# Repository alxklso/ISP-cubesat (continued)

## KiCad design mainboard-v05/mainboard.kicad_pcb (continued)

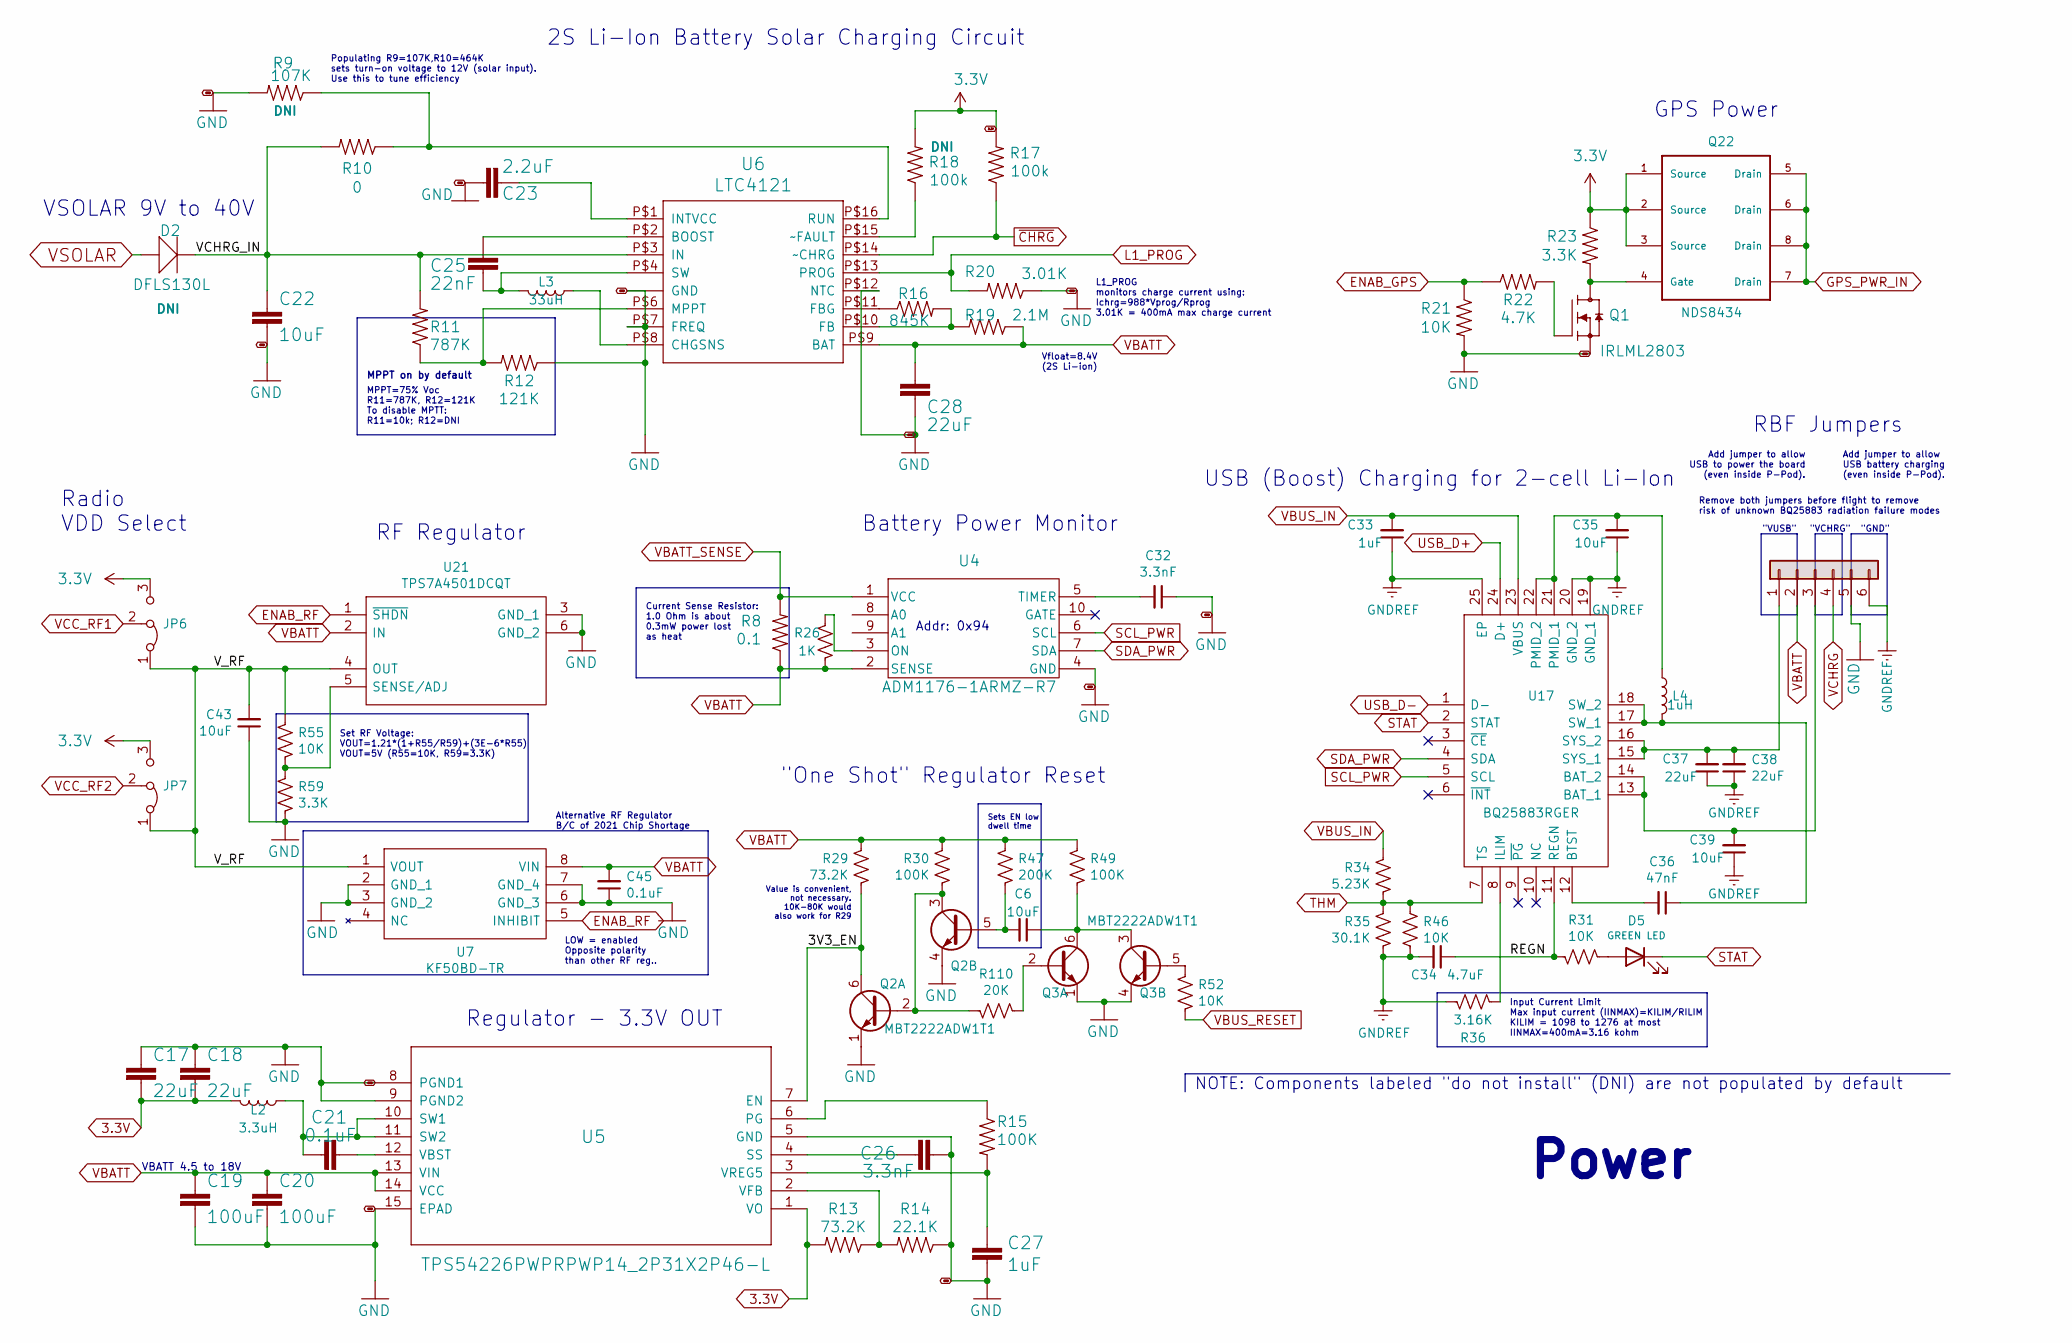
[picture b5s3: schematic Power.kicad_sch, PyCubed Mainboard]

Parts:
C6, C22, C35, C39, C43: 10uF; C_0603_1608Metric
C17, C18, C28, C37, C38: 22uF; C_0603_1608Metric
C19, C20: 100uF; C_1210_3225Metric
C21, C45: 0.1uF; C_0603_1608Metric
C23: 2.2uF; C_0603_1608Metric
C25: 22nF; C_0603_1608Metric
C26, C32: 3.3nF; C_0603_1608Metric
C27, C33: 1uF; C_0603_1608Metric
C34: 4.7uF; C_0603_1608Metric
C36: 47nF; C_0603_1608Metric
D2: DFLS130L; PWRDI-123; Manufacturer_Part_Number DFLS130L-7
D5: GREEN LED; LED_0603_1608Metric; Manufacturer_Part_Number LTST-C190KGKT
J14: Conn_01x06; PinHeader_1x06_P2.54mm_Vertical
JP6, JP7: Jumper_3_Bridged12; SolderJumper-3_P1.3mm_Bridged12_RoundedPad1.0x1.5mm
L2: 3.3uH; L_2141; Manufacturer_Part_Number HPC5040NF-3R3MTH
L3: 33uH; L_1812_4532Metric; Manufacturer_Part_Number SNR5040K-330M
L4: 1uH; L_2510; Manufacturer_Part_Number MCS25GD-1R0MMP
Q1: IRLML2803; SOT-23; Manufacturer_Part_Number IRLML2803TRPbF
Q2, Q3: MBT2222ADW1T1; SOT-363_SC-70-6; Manufacturer_Part_Number MBT2222ADW1T1G
Q22: NDS8434; Manufacturer_Part_Number NDS8434
R8: 0.1; R_2512_6332Metric
R9: 107K; R_0603_1608Metric
R10: 0; R_0603_1608Metric
R11: 787K; R_0603_1608Metric
R12: 121K; R_0603_1608Metric
R13, R29: 73.2K; R_0603_1608Metric
R14: 22.1K; R_0603_1608Metric
R15, R30, R49: 100K; R_0603_1608Metric
R16: 845K; R_0603_1608Metric
R17, R18: 100k; R_0603_1608Metric
R19: 2.1M; R_0603_1608Metric
R20: 3.01K; R_0603_1608Metric
R21, R31, R46, R52, R55: 10K; R_0603_1608Metric
R22: 4.7K; R_0603_1608Metric
R23, R59: 3.3K; R_0603_1608Metric
R26: 1K; R_0603_1608Metric
R34: 5.23K; R_0603_1608Metric
R35: 30.1K; R_0603_1608Metric
R36: 3.16K; R_0603_1608Metric
R47: 200K; R_0603_1608Metric
R110: 20K; R_0603_1608Metric
U4: ADM1176-1ARMZ-R7; Manufacturer_Part_Number ADM1176-1ARMZ-R7
U5: TPS54226PWPRPWP14_2P31X2P46-L; PWP14_2P31X2P46-L; Manufacturer_Part_Number TPS54226PWPR
U6: LTC4121; QFN-16-PAD; Manufacturer_Part_Number LTC4121EUD
U7: KF50BD-TR; SOIC127P600X175-8N; Manufacturer_Part_Number KF50BD-TR
U17: BQ25883RGER; QFN50P400X400X100-25N-D; Manufacturer_Part_Number BQ25883RGER
U21: TPS7A4501DCQT; Manufacturer_Part_Number TPS7A4501DCQT

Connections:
3.3V: C17.2, C18.2, JP6.3 (B), JP7.3 (B), L2.2, Q22.1 (Source), Q22.2 (Source), Q22.3 (Source), R13.2, R17.2, R18.2, R23.1, U5.1 (VO); also elsewhere on the board
/Power/3V3_EN: Q2.6 (C1), R29.2, U5.7 (EN)
/Power/REGN: C34.1, R31.2, U17.11 (REGN)
/Power/VCHRG_IN: C22.1, D2.C, R10.2, R11.2, U6.P$3 (IN)
/Power/V_RF: C43.2, JP6.1 (A), JP7.1 (A), R55.1, U7.1 (VOUT), U21.4 (OUT)
ENAB_GPS: R21.1, R22.1; also elsewhere on the board
ENAB_RF: U7.5 (INHIBIT), U21.1 (~SHDN); also elsewhere on the board
GND: C17.1, C18.1, C19.2, C20.2, C22.2, C23.2, C26.2, C27.2, C28.2, C32.1, C43.1, C45.1, J14.5, Q1.2 (S), Q2.1 (E1), Q2.4 (E2), Q3.1 (E1), Q3.4 (E2), R9.2, R12.1, R14.1, R20.1, R21.2, R59.2, U4.4 (GND), U5.5 (GND), U5.8 (PGND1), U5.9 (PGND2), U5.15 (EPAD), U6.P$5 (GND), U6.P$7 (FREQ), U6.P$12 (NTC), U6.P$17 (GND), U7.2 (GND_1), U7.3 (GND_2), U7.6 (GND_3), U7.7 (GND_4), U21.3 (GND_1), U21.6 (GND_2); also elsewhere on the board
GNDREF: C33.1, C34.2, C35.1, C37.1, C38.1, C39.1, J14.6, R35.1, R36.1, R46.1, U17.19 (GND_1), U17.20 (GND_2), U17.25 (EP); also elsewhere on the board
GPS_PWR_IN: Q22.5 (Drain), Q22.6 (Drain), Q22.7 (Drain), Q22.8 (Drain); also elsewhere on the board
L1_PROG: R20.2, U6.P$13 (PROG); also elsewhere on the board
unnamed: C6.1, Q3.3 (C2), Q3.6 (C1), R49.2
unnamed: C6.2, Q2.5 (B2), R47.2
unnamed: C21.1, L2.1, U5.10 (SW1), U5.11 (SW2)
unnamed: C21.2, U5.12 (VBST)
unnamed: C23.1, U6.P$1 (INTVCC)
unnamed: C25.1, U6.P$2 (BOOST)
unnamed: C25.2, L3.2, U6.P$4 (SW)
unnamed: C26.1, U5.4 (SS)
unnamed: C27.1, R15.2, U5.3 (VREG5)
unnamed: C32.2, U4.5 (TIMER)
unnamed: C35.2, L4.1, U17.21 (PMID_1), U17.22 (PMID_2)
unnamed: C36.1, L4.2, U17.17 (SW_1), U17.18 (SW_2)
unnamed: C36.2, U17.12 (BTST)
unnamed: C37.2, C38.2, J14.1, U17.15 (SYS_1), U17.16 (SYS_2)
unnamed: C39.2, J14.3, U17.13 (BAT_1), U17.14 (BAT_2)
unnamed: D5.2 (A), R31.1
unnamed: L3.1, U6.P$8 (CHGSNS)
unnamed: Q1.1 (G), R22.2
unnamed: Q1.3 (D), Q22.4 (Gate), R23.2
unnamed: Q2.2 (B1), Q2.3 (C2), R30.2, R110.2
unnamed: Q3.2 (B1), R110.1
unnamed: Q3.5 (B2), R52.1
unnamed: R9.1, R10.1, U6.P$16 (RUN)
unnamed: R11.1, R12.2, U6.P$6 (MPPT)
unnamed: R13.1, R14.2, U5.2 (VFB)
unnamed: R15.1, U5.6 (PG)
unnamed: R16.1, U6.P$11 (FBG)
unnamed: R16.2, R19.2, U6.P$10 (FB)
unnamed: R18.1, U6.P$15 (~FAULT)
unnamed: R26.2, U4.3 (ON)
unnamed: R36.2, U17.8 (ILIM)
unnamed: R55.2, R59.1, U21.5 (SENSE/ADJ)
SCL_PWR: U4.6 (SCL), U17.5 (SCL); also elsewhere on the board
SDA_PWR: U4.7 (SDA), U17.4 (SDA); also elsewhere on the board
STAT: D5.1 (K), U17.2 (STAT)
THM: R34.2, R35.2, R46.2, U17.7 (TS)
USB_D+: U17.24 (D+); also elsewhere on the board
USB_D-: U17.1 (D-); also elsewhere on the board
VBATT: C19.1, C20.1, C28.1, C45.2, J14.2, R8.1, R19.1, R26.1, R29.1, R30.1, R47.1, R49.1, U4.2 (SENSE), U5.13 (VIN), U5.14 (VCC), U6.P$9 (BAT), U7.8 (VIN), U21.2 (IN); also elsewhere on the board
VBATT_SENSE: R8.2, U4.1 (VCC); also elsewhere on the board
VBUS_IN: C33.2, R34.1, U17.23 (VBUS); also elsewhere on the board
VBUS_RESET: R52.2; also elsewhere on the board
VCC_RF1: JP6.2 (C); also elsewhere on the board
VCC_RF2: JP7.2 (C); also elsewhere on the board
VCHRG: J14.4; also elsewhere on the board
VSOLAR: D2.A; also elsewhere on the board
~CHRG: R17.1, U6.P$14 (~CHRG); also elsewhere on the board

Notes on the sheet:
Populating R9=107K,R10=464K sets turn-on voltage to 12V (solar input). Use this to tune efficiency
Set RF Voltage: VOUT=1.21*(1+R55/R59)+(3E-6*R55) VOUT=5V (R55=10K, R59=3.3K)
Vfloat=8.4V (2S Li-ion)
"One Shot" Regulator Reset
Battery Power Monitor
Value is convenient, not necessary. 10K-80K would also work for R29
MPPT=75% Voc R11=787K, R12=121K To disable MPTT: R11=10k; R12=DNI
"GND"
"VUSB"
L1_PROG monitors charge current using: Ichrg=988*Vprog/Rprog 3.01K = 400mA max charge current
Regulator - 3.3V OUT
Alternative RF Regulator B/C of 2021 Chip Shortage
Remove both jumpers before flight to remove risk of unknown BQ25883 radiation failure modes
NOTE: Components labeled "do not install" (DNI) are not populated by default
Input Current Limit Max input current (IINMAX)=KILIM/RILIM KILIM = 1098 to 1276 at most IINMAX=400mA=3.16 kohm
Power
RBF Jumpers
Addr: 0x94
VSOLAR 9V to 40V
GPS Power
LOW = enabled Opposite polarity than other RF reg..
2S Li-Ion Battery Solar Charging Circuit
Add jumper to allow USB to power the board (even inside P-Pod).
USB (Boost) Charging for 2-cell Li-Ion
RF Regulator
Radio VDD Select
"VCHRG"
Sets EN low dwell time
Add jumper to allow USB battery charging (even inside P-Pod).
MPPT on by default
VBATT 4.5 to 18V
Current Sense Resistor: 1.0 Ohm is about 0.3mW power lost as heat

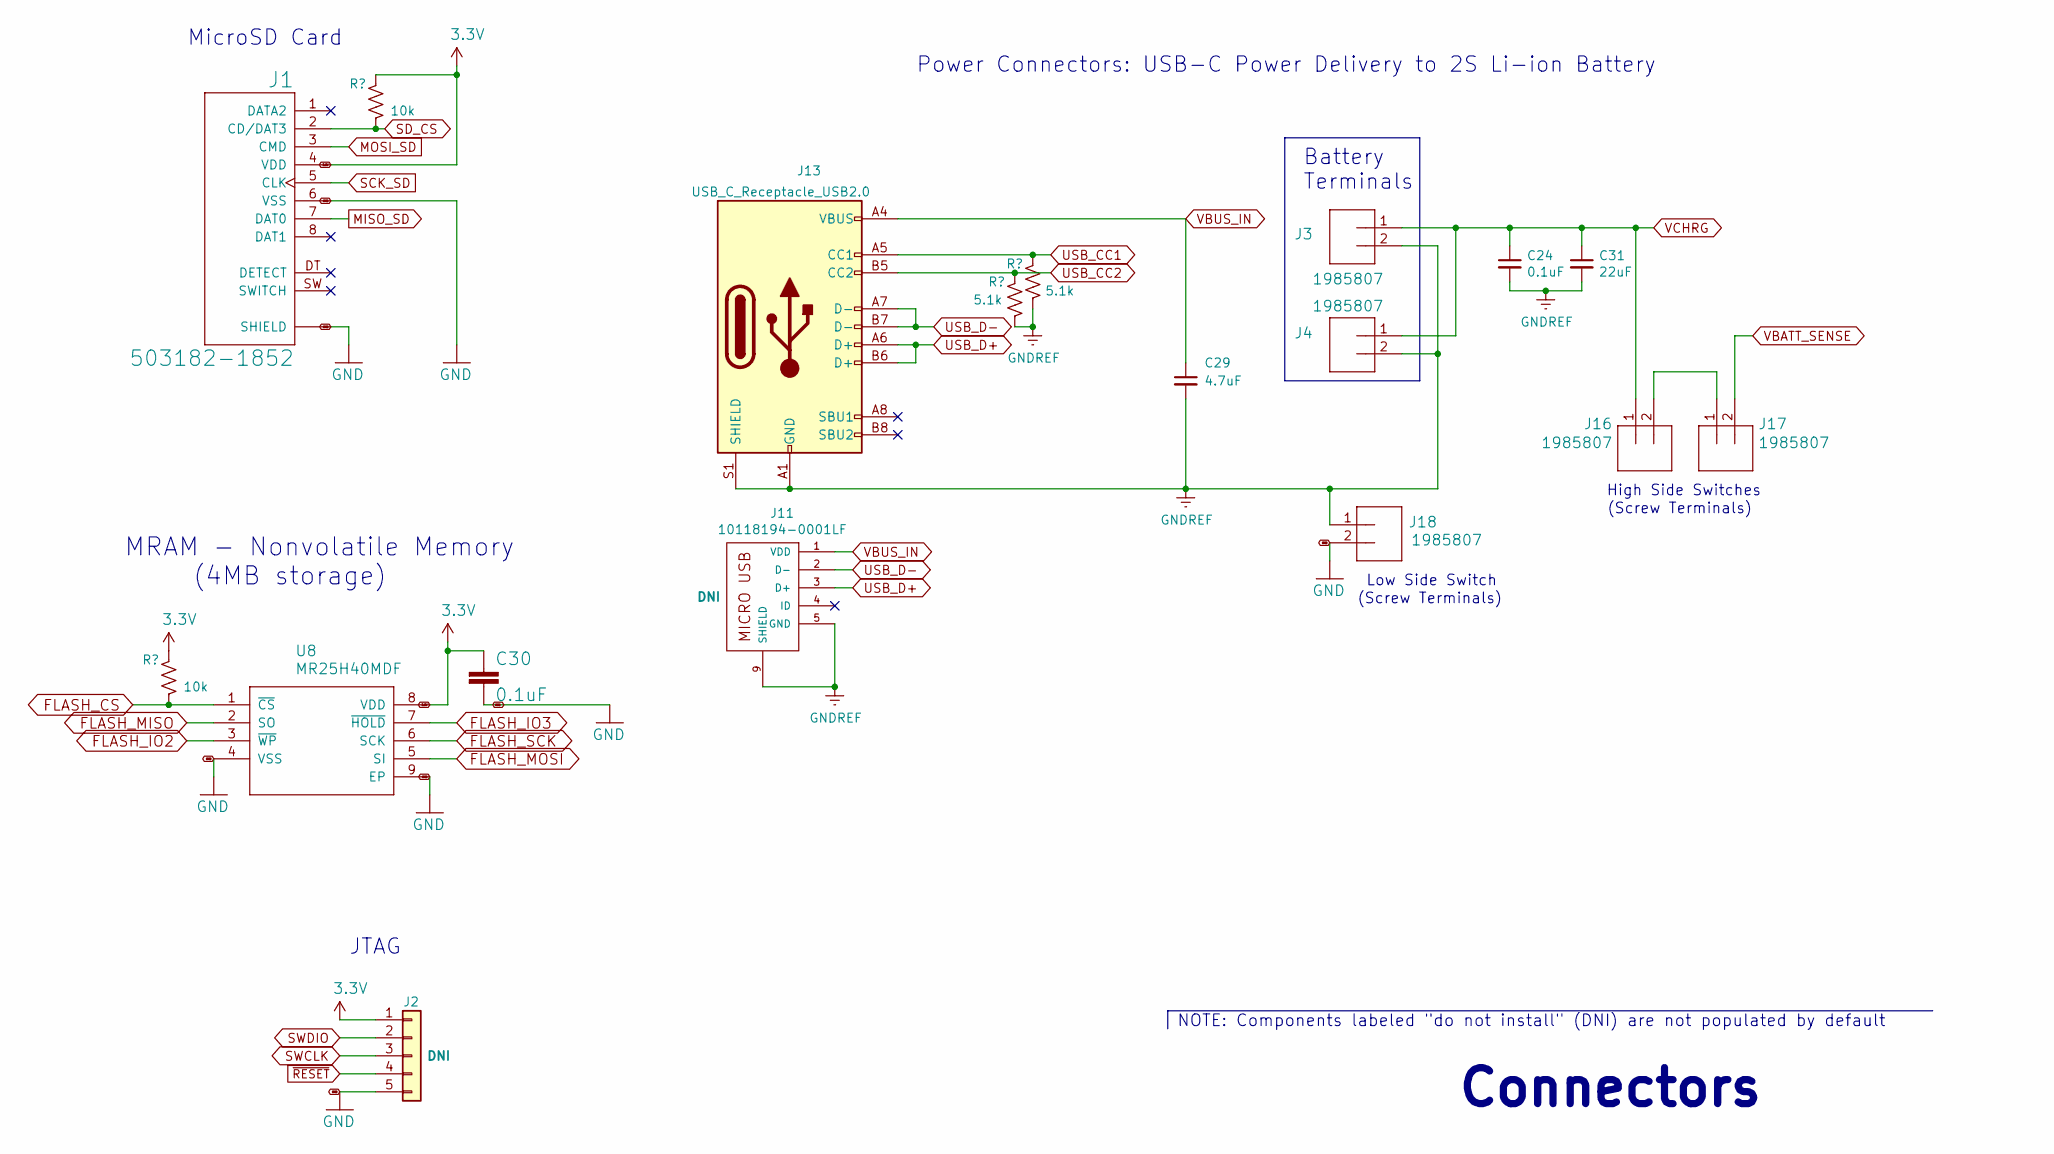
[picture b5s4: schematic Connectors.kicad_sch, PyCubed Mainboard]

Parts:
C24, C30: 0.1uF; C_0603_1608Metric
C29: 4.7uF; C_0603_1608Metric
C31: 22uF; C_0603_1608Metric
J1: 503182-1852; MOLEX_503182-1852; Manufacturer_Part_Number 5031821852
J2: Conn_01x05; PinHeader_1x05_P2.54mm_Vertical
J3, J4, J16, J17, J18: 1985807; SCREWTERMINAL-3.5MM-2_LOCK; Manufacturer_Part_Number 1985807
J11: 10118194-0001LF
J13: USB_C_Receptacle_USB2.0; USB_C_Receptacle_XKB_U262-161N-4BVC11; Manufacturer_Part_Number U262-161N-4BVC11
R39, R40: 5.1k; R_0603_1608Metric
R50, R51: 10k; R_0603_1608Metric
U8: MR25H40MDF; SON127P600X500X90-9N; Manufacturer_Part_Number W25Q80DVSNIG

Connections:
3.3V: C30.1, J1.4 (VDD), J2.1, R50.2, R51.2, U8.8 (VDD); also elsewhere on the board
FLASH_CS: R50.1, U8.1 (~CS); also elsewhere on the board
FLASH_IO2: U8.3 (~WP); also elsewhere on the board
FLASH_IO3: U8.7 (~HOLD); also elsewhere on the board
FLASH_MISO: U8.2 (SO); also elsewhere on the board
FLASH_MOSI: U8.5 (SI); also elsewhere on the board
FLASH_SCK: U8.6 (SCK); also elsewhere on the board
GND: C30.2, J1.6 (VSS), J1.P1 (SHIELD), J1.P2 (SHIELD), J1.P3 (SHIELD), J1.P4 (SHIELD), J1.P5 (SHIELD), J2.5, J18.2, U8.4 (VSS), U8.9 (EP); also elsewhere on the board
GNDREF: C24.2, C29.2, C31.2, J3.2, J4.2, J11.5 (GND), J11.8, J11.9 (SHIELD), J13.A1 (GND), J13.A12 (GND), J13.B1 (GND), J13.B12 (GND), J13.S1 (SHIELD), J18.1, R39.1, R40.1; also elsewhere on the board
MISO_SD: J1.7 (DAT0); also elsewhere on the board
MOSI_SD: J1.3 (CMD); also elsewhere on the board
unnamed: J16.2, J17.1
SCK_SD: J1.5 (CLK); also elsewhere on the board
SD_CS: J1.2 (CD/DAT3), R51.1; also elsewhere on the board
SWCLK: J2.3; also elsewhere on the board
SWDIO: J2.2; also elsewhere on the board
USB_CC1: J13.A5 (CC1), R40.2
USB_CC2: J13.B5 (CC2), R39.2
USB_D+: J11.3 (D+), J13.A6 (D+), J13.B6 (D+); also elsewhere on the board
USB_D-: J11.2 (D-), J13.A7 (D-), J13.B7 (D-); also elsewhere on the board
VBATT_SENSE: J17.2; also elsewhere on the board
VBUS_IN: C29.1, J11.1 (VDD), J13.A4 (VBUS), J13.A9 (VBUS), J13.B4 (VBUS), J13.B9 (VBUS); also elsewhere on the board
VCHRG: C24.1, C31.1, J3.1, J4.1, J16.1; also elsewhere on the board
~RESET: J2.4; also elsewhere on the board

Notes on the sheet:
Power Connectors: USB-C Power Delivery to 2S Li-ion Battery
(Screw Terminals)
NOTE: Components labeled "do not install" (DNI) are not populated by default
Connectors
Low Side Switch
JTAG
MRAM - Nonvolatile Memory (4MB storage)
Battery Terminals
High Side Switches
MicroSD Card

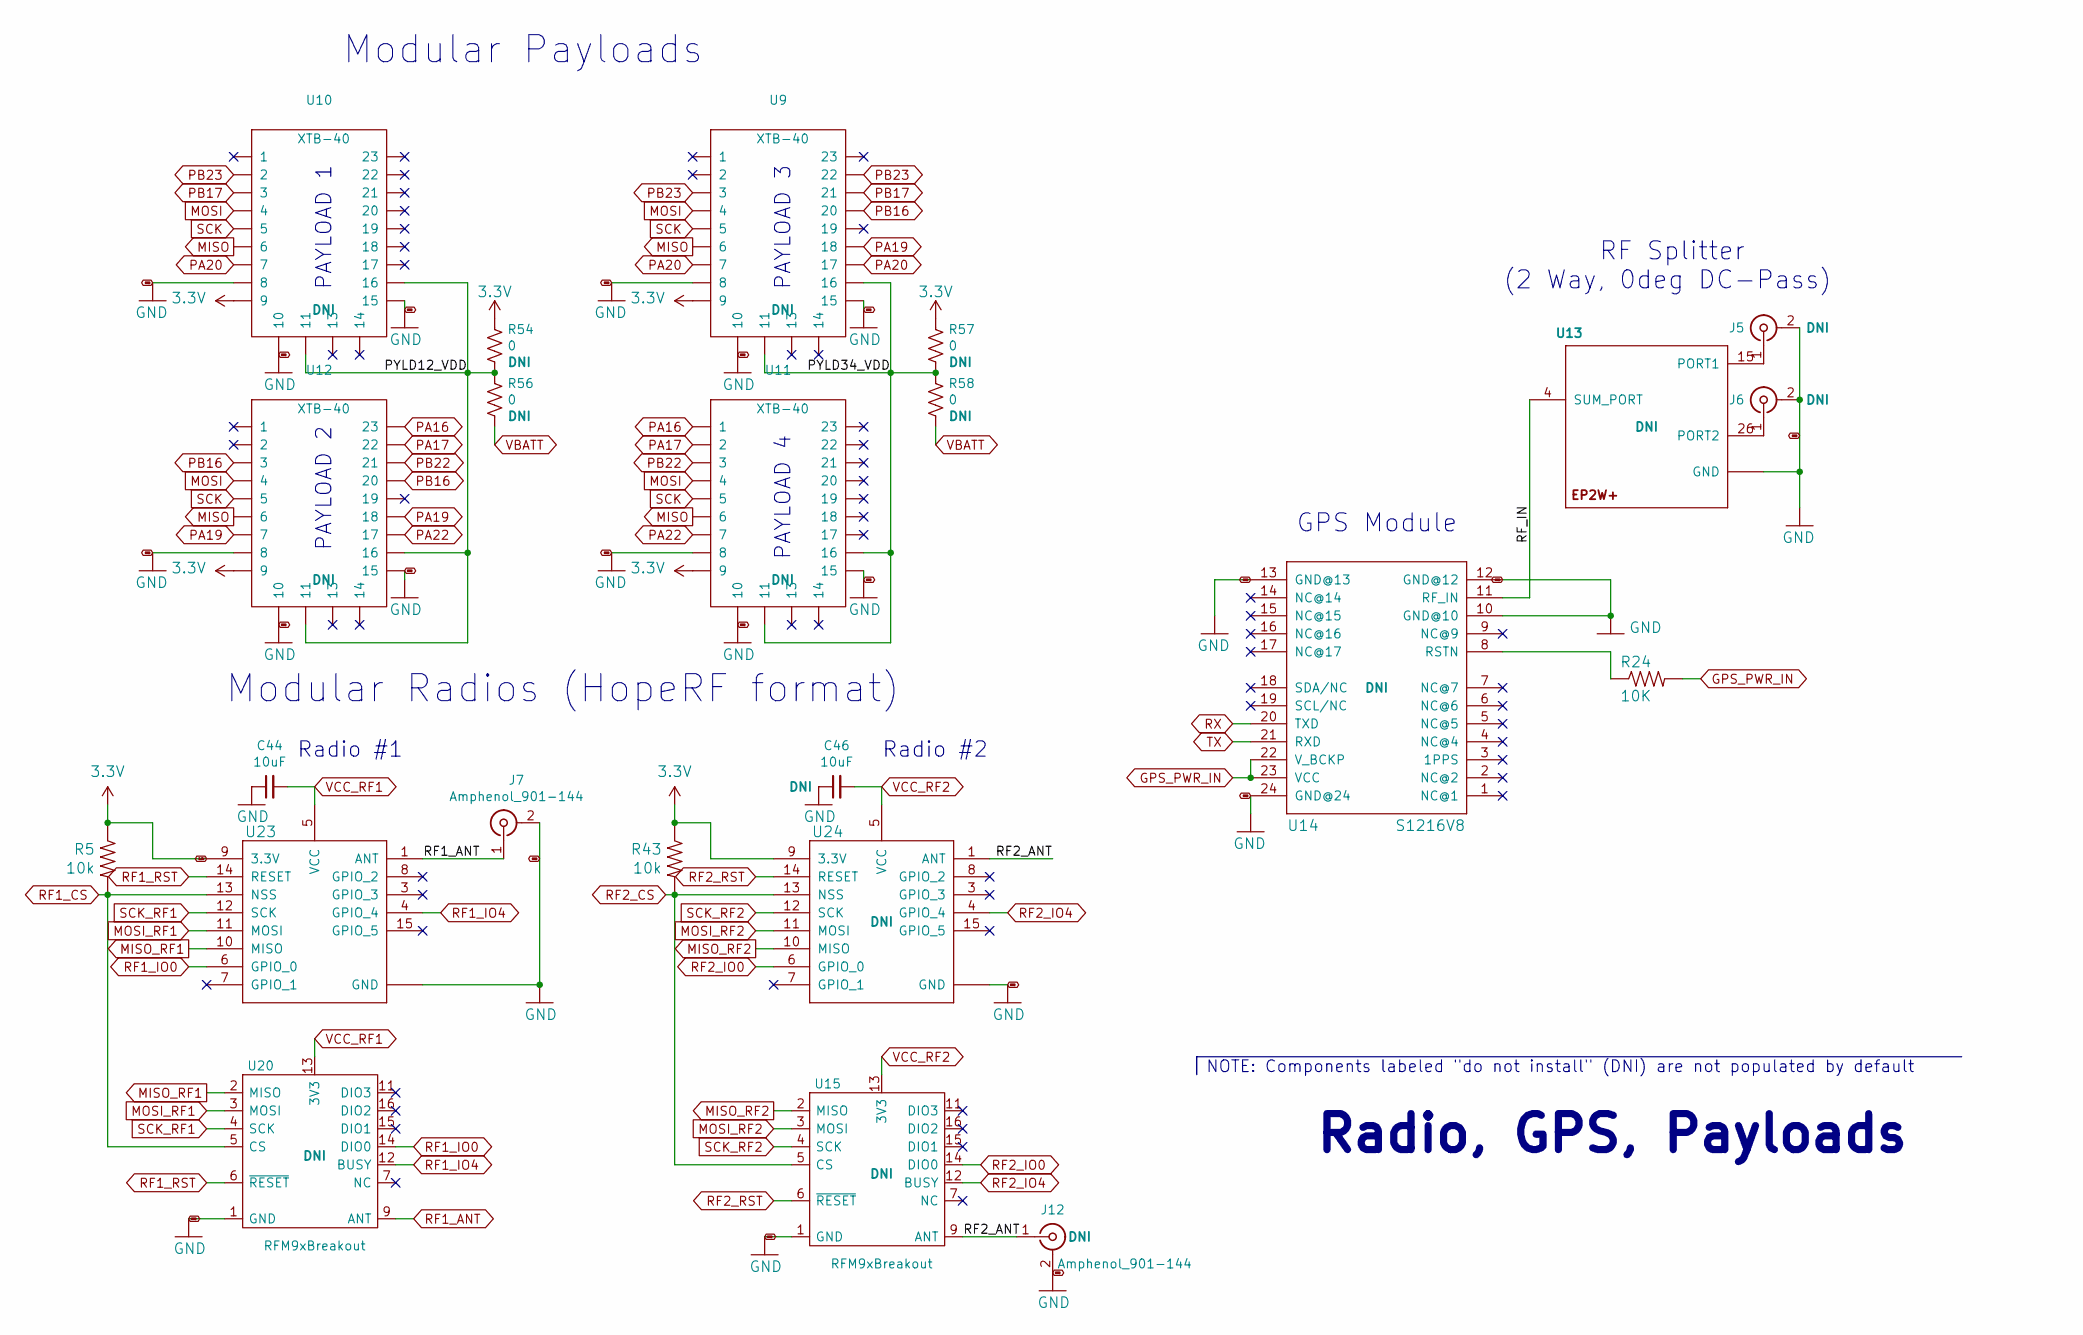
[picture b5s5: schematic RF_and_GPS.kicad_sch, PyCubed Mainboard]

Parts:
C44, C46: 10uF; C_0603_1608Metric
J5, J6, J7, J12: Amphenol_901-144; SMA_Amphenol_901-144_Vertical; Manufacturer_Part_Number 901-144
R5, R43: 10k; R_0603_1608Metric
R24: 10K; R_0603_1608Metric
R54, R56, R57, R58: 0; R_0805_2012Metric
U9, U10, U11, U12: XTB-40; XTB40_payload
U13: EP2W+; QFN32-5X5MM; Manufacturer_Part_Number EP2W+
U14: S1216V8; S1216_24PIN_PACKAGE
U15, U20: RFM9xBreakout; HOPERF_RFM9XW_SMD
U23: RFM98PW; RFM95PW; Manufacturer_Part_Number RFM98PW
U24: RFM98PW; RFM95PW

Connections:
3.3V: R5.1, R43.1, R54.1, R57.1, U9.9, U10.9, U11.9, U12.9, U23.9 (3.3V), U24.9 (3.3V); also elsewhere on the board
/RF and GPS/PYLD12_VDD: R54.2, R56.1, U10.11, U10.16, U12.11, U12.16
/RF and GPS/PYLD34_VDD: R57.2, R58.1, U9.11, U9.16, U11.11, U11.16
/RF and GPS/RF2_ANT: J12.1 (In), U15.9 (ANT), U24.1 (ANT)
/RF and GPS/RF_IN: U13.4 (SUM_PORT), U14.11 (RF_IN)
GND: C44.1, C46.1, J5.2 (Ext), J6.2 (Ext), J7.2 (Ext), J12.2 (Ext), U9.8, U9.10, U9.15, U10.8, U10.10, U10.15, U11.8, U11.10, U11.15, U12.8, U12.10, U12.15, U13.1 (GND), U13.2 (GND), U13.3 (GND), U13.5 (GND), U13.6 (GND), U13.7 (GND), U13.8 (GND), U13.9 (GND), U13.10 (GND), U13.11 (GND), U13.12 (GND), U13.13 (GND), U13.14 (GND), U13.16 (GND), U13.17 (GND), U13.18 (GND), U13.19 (GND), U13.20 (GND), U13.21 (GND), U13.22 (GND), U13.23 (GND), U13.24 (GND), U13.25 (GND), U13.27 (GND), U13.28 (GND), U13.29 (GND), U13.30 (GND), U13.31 (GND), U13.32 (GND), U13.EP (GND), U14.10 (GND@10), U14.12 (GND@12), U14.13 (GND@13), U14.24 (GND@24), U15.1 (GND), U15.8 (GND), U15.10 (GND), U20.1 (GND), U20.8 (GND), U20.10 (GND), U23.2 (GND), U23.16 (GND), U23.17 (GND), U24.2 (GND), U24.16 (GND), U24.17 (GND); also elsewhere on the board
GPS_PWR_IN: R24.2, U14.22 (V_BCKP), U14.23 (VCC); also elsewhere on the board
MISO: U9.6, U10.6, U11.6, U12.6; also elsewhere on the board
MISO_RF1: U20.2 (MISO), U23.10 (MISO); also elsewhere on the board
MISO_RF2: U15.2 (MISO), U24.10 (MISO); also elsewhere on the board
MOSI: U9.4, U10.4, U11.4, U12.4; also elsewhere on the board
MOSI_RF1: U20.3 (MOSI), U23.11 (MOSI); also elsewhere on the board
MOSI_RF2: U15.3 (MOSI), U24.11 (MOSI); also elsewhere on the board
unnamed: J5.1 (In), U13.15 (PORT1)
unnamed: J6.1 (In), U13.26 (PORT2)
unnamed: R24.1, U14.8 (RSTN)
PA16: U11.1, U12.23; also elsewhere on the board
PA17: U11.2, U12.22; also elsewhere on the board
PA19: U9.18, U12.7, U12.18; also elsewhere on the board
PA20: U9.7, U9.17, U10.7; also elsewhere on the board
PA22: U11.7, U12.17; also elsewhere on the board
PB16: U9.20, U12.3, U12.20; also elsewhere on the board
PB17: U9.21, U10.3; also elsewhere on the board
PB22: U11.3, U12.21; also elsewhere on the board
PB23: U9.3, U9.22, U10.2; also elsewhere on the board
RF1_ANT: J7.1 (In), U23.1 (ANT)
RF1_CS: R5.2, U20.5 (CS), U23.13 (NSS); also elsewhere on the board
RF1_IO0: U20.14 (DIO0), U23.6 (GPIO_0); also elsewhere on the board
RF1_IO4: U20.12 (BUSY), U23.4 (GPIO_4); also elsewhere on the board
RF1_RST: U20.6 (~RESET), U23.14 (RESET); also elsewhere on the board
RF2_CS: R43.2, U15.5 (CS), U24.13 (NSS); also elsewhere on the board
RF2_IO0: U15.14 (DIO0), U24.6 (GPIO_0); also elsewhere on the board
RF2_IO4: U15.12 (BUSY), U24.4 (GPIO_4); also elsewhere on the board
RF2_RST: U15.6 (~RESET), U24.14 (RESET); also elsewhere on the board
RX: U14.20 (TXD); also elsewhere on the board
SCK: U9.5, U10.5, U11.5, U12.5; also elsewhere on the board
SCK_RF1: U20.4 (SCK), U23.12 (SCK); also elsewhere on the board
SCK_RF2: U15.4 (SCK), U24.12 (SCK); also elsewhere on the board
TX: U14.21 (RXD); also elsewhere on the board
VBATT: R56.2, R58.2; also elsewhere on the board
VCC_RF1: C44.2, U20.13 (3V3), U23.5 (VCC); also elsewhere on the board
VCC_RF2: C46.2, U15.13 (3V3), U24.5 (VCC); also elsewhere on the board

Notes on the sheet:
RF Splitter (2 Way, 0deg DC-Pass)
Modular Payloads
NOTE: Components labeled "do not install" (DNI) are not populated by default
PAYLOAD 4
PAYLOAD 2
Radio #2
Radio, GPS, Payloads
GPS Module
PAYLOAD 3
Radio #1
PAYLOAD 1
Modular Radios (HopeRF format)

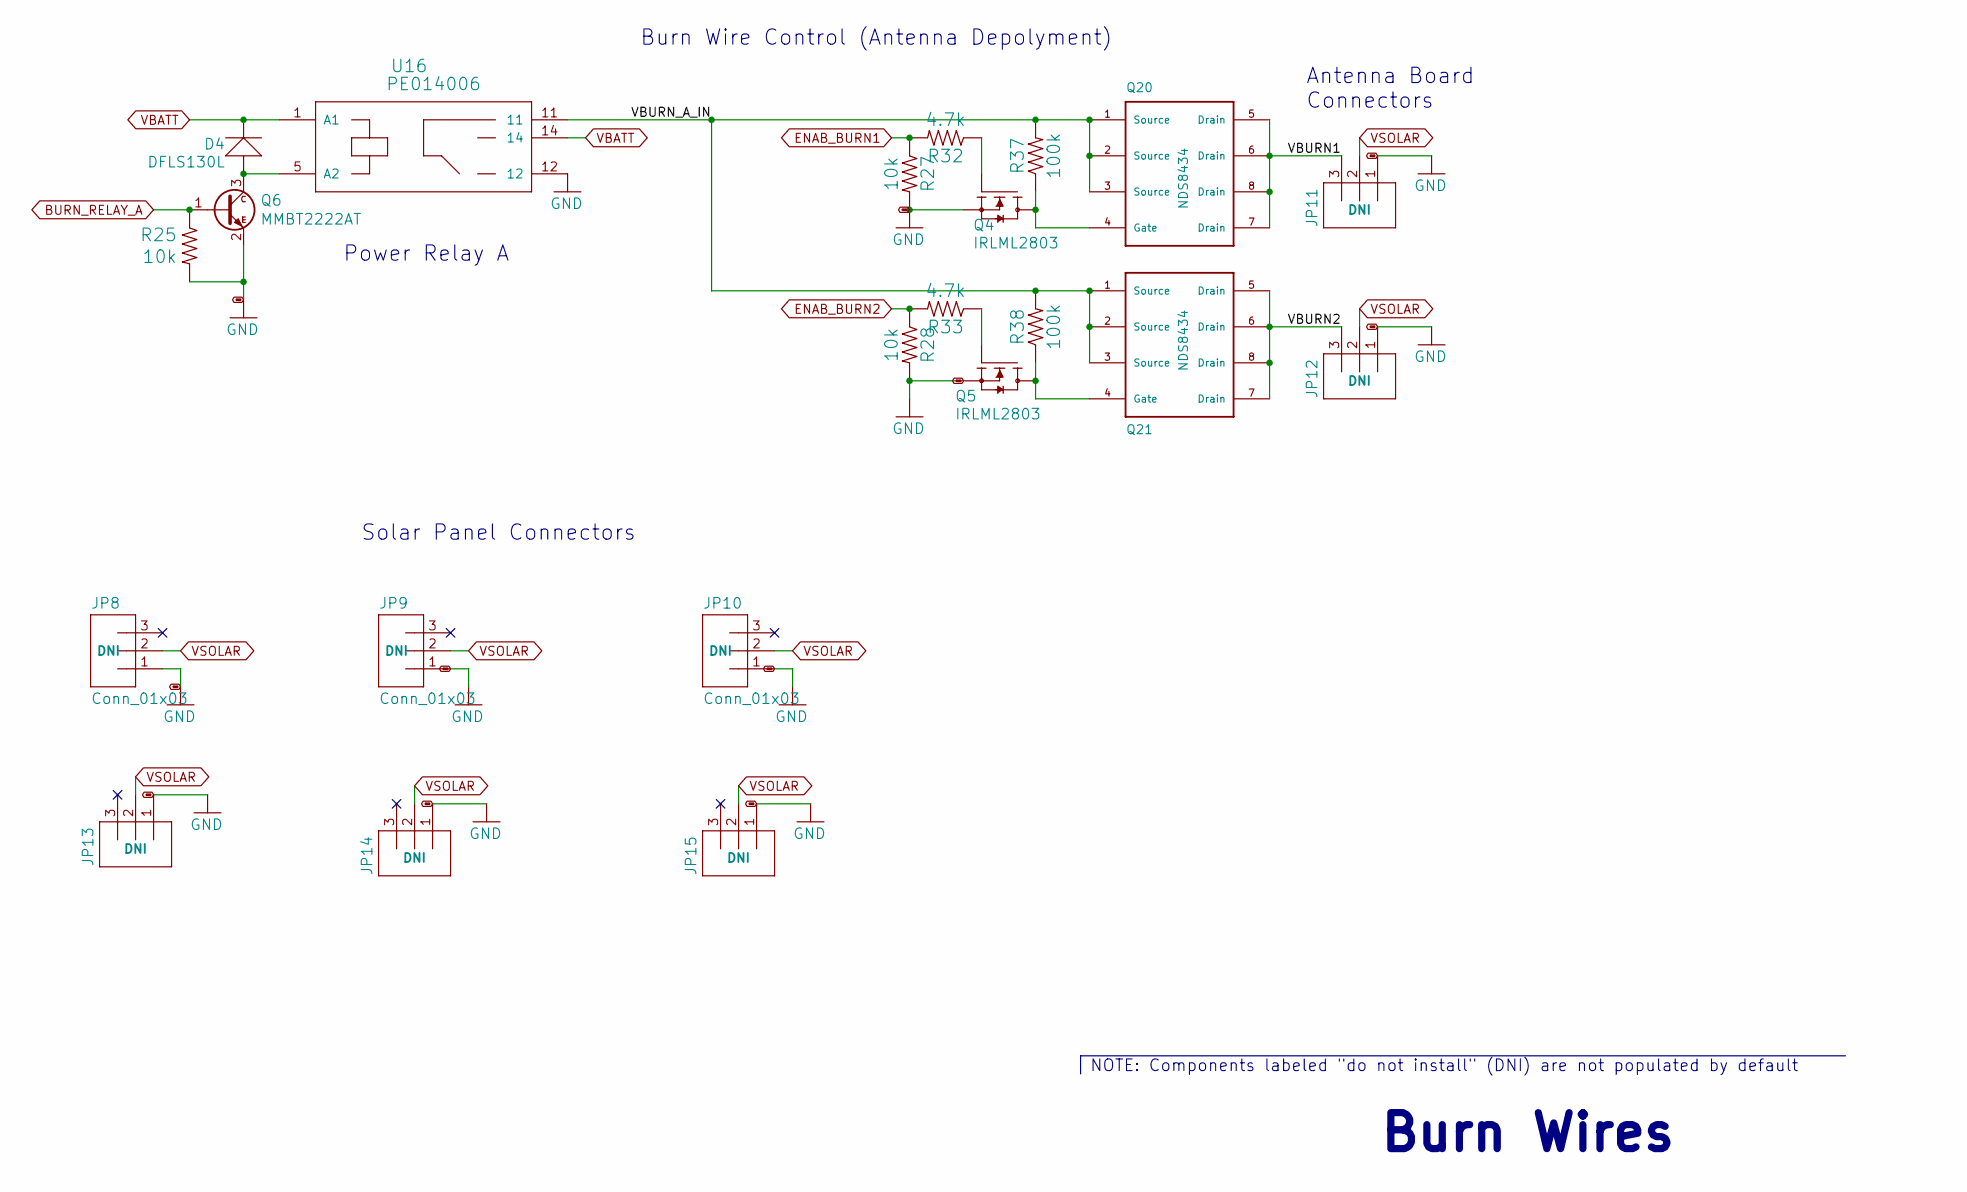
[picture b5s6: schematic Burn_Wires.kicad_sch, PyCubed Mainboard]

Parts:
D4: DFLS130L; PWRDI-123; Manufacturer_Part_Number DFLS130L-7
JP8, JP9, JP10, JP11, JP12, JP13, JP14, JP15: Conn_01x03; MOLEX-1X3_LOCK; Manufacturer_Part_Number 22-23-2037
Q4: IRLML2803; SOT-23; Manufacturer_Part_Number IRLML2803TRPbF
Q5: IRLML2803; SOT-23; Manufacturer_Part_Number MMBT2222AT
Q6: MMBT2222AT; SOT-23; Manufacturer_Part_Number MMBT2222ALT1G
Q20, Q21: NDS8434; Manufacturer_Part_Number NDS8434
R25, R27, R28: 10k; R_0603_1608Metric
R32, R33: 4.7k; R_0603_1608Metric
R37, R38: 100k; R_0603_1608Metric
U16: PE014006; RELAY_PE014006; Manufacturer_Part_Number PE014006 TE

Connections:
/Burn Wires/VBURN1: JP11.3, Q20.5 (Drain), Q20.6 (Drain), Q20.7 (Drain), Q20.8 (Drain)
/Burn Wires/VBURN2: JP12.3, Q21.5 (Drain), Q21.6 (Drain), Q21.7 (Drain), Q21.8 (Drain)
/Burn Wires/VBURN_A_IN: Q20.1 (Source), Q20.2 (Source), Q20.3 (Source), Q21.1 (Source), Q21.2 (Source), Q21.3 (Source), R37.2, R38.2, U16.11
BURN_RELAY_A: Q6.1 (B), R25.1; also elsewhere on the board
ENAB_BURN1: R27.1, R32.2; also elsewhere on the board
ENAB_BURN2: R28.1, R33.2; also elsewhere on the board
GND: JP8.1, JP9.1, JP10.1, JP11.1, JP12.1, JP13.1, JP14.1, JP15.1, Q4.2 (S), Q5.2 (S), Q6.2 (E), R25.2, R27.2, R28.2, U16.12; also elsewhere on the board
unnamed: D4.A, Q6.3 (C), U16.5 (A2)
unnamed: Q4.1 (G), R32.1
unnamed: Q5.1 (G), R33.1
unnamed: Q4.3 (D), Q20.4 (Gate), R37.1
unnamed: Q5.3 (D), Q21.4 (Gate), R38.1
VBATT: D4.C, U16.1 (A1), U16.14; also elsewhere on the board
VSOLAR: JP8.2, JP9.2, JP10.2, JP11.2, JP12.2, JP13.2, JP14.2, JP15.2; also elsewhere on the board

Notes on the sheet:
Antenna Board Connectors
Solar Panel Connectors
Burn Wires
Power Relay A
NOTE: Components labeled "do not install" (DNI) are not populated by default
Burn Wire Control (Antenna Depolyment)
